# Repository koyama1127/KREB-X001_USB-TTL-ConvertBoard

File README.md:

CH340を使用したUSBシリアル変換機  
設計者の在庫部品の都合上リード部品を多用  
今後別バージョンでSMDを使用した小型バージョンも作成予定  

備考　USBコネクタを今後Type-Cにしたい  

追記　別リポジトリ KREB-X001-2にSMD統一かつUSB Type-C Verを試作中

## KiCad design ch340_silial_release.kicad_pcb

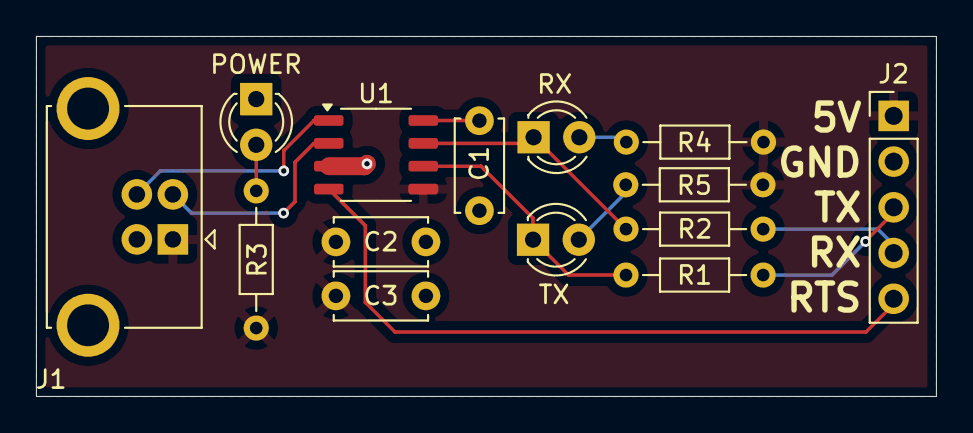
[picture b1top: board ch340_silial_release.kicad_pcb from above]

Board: 2 copper layers, 50.0 x 20.0 mm, 14 parts (0 on the bottom side), 13 nets.

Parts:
C1: 1000pF; C_Disc_D5.0mm_W2.5mm_P5.00mm
C2: 0.1uF; C_Disc_D5.0mm_W2.5mm_P5.00mm
C3: 10uF; C_Disc_D5.0mm_W2.5mm_P5.00mm
J1: USB_B; USB_B_OST_USB-B1HSxx_Horizontal
J2: Conn_01x05_Pin; PinHeader_1x05_P2.54mm_Vertical
POWER: LED; LED_D3.0mm
R1, R2, R3, R4, R5: 1k; R_Axial_DIN0204_L3.6mm_D1.6mm_P7.62mm_Horizontal
RX: LED; LED_D3.0mm
TX: LED; LED_D3.0mm
U1: CH340N; SOP-8_3.9x4.9mm_P1.27mm

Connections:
5V: C2.2, C3.2, J1.1 (VBUS), J2.1, R3.1, R4.2, R5.2, U1.5 (VCC)
unnamed: POWER.2 (A), R3.2
unnamed: R5.1, TX.2 (A)
unnamed: R1.2, TX.1 (K), U1.6 (TXD)
unnamed: R4.1, RX.2 (A)
unnamed: R2.2, RX.1 (K), U1.7 (RXD)
unnamed: J1.3 (D+), U1.1 (UD+)
unnamed: J1.2 (D-), U1.2 (UD-)
unnamed: C1.1, U1.8 (V3)
gnd: C1.2, C2.1, C3.1, J1.4 (GND), J1.5 (Shield), J2.2, POWER.1 (K), U1.3 (GND)
reset: J2.5, U1.4 (~RTS)
rx: J2.4, R2.1
tx: J2.3, R1.1

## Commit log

2025-02-06 test_relese
2025-02-06 gitignore変更
2025-02-12 フットプリント修正
